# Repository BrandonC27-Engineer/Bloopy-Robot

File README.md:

# Bloopy 🤖
### An AI Companion Robot Prototype

**Designed and built by Brandon Carmona Guerena**

Bloopy is a personal robotics project exploring how electronics,
physical interaction, and artificial intelligence can work together
to create a more expressive companion.

The project began with an idea: What if a digital companion could
eventually have a physical presence and interact with its surroundings?

I developed a stationary working prototype to explore that idea,
combining custom hardware, sensors, a Raspberry Pi, an ESP32,
animated eyes, and an AI-assisted companion application.

---

## What the Prototype Does

The stationary Bloopy prototype integrates:

- **ESP32:** Collects sensor readings and controls OLED eye animations.
- **Raspberry Pi 4:** Handles higher-level processing and connected peripherals.
- **Sensors:** Detect environmental conditions and nearby objects.
- **OLED eyes:** Display expressions and animations in response to interactions.
- **Camera and microphone:** Support visual and audio input.
- **Speaker:** Provides audio output.
- **Companion application:** Provides controls, displays information, and
  communicates with the robot.
- **AI API integration:** Supports context-aware companion responses.

The application and hardware communicate to create an interactive
experience rather than a standalone chatbot.

## My Design and Building Process

I developed Bloopy through an iterative process involving:

1. Planning the robot's capabilities and component architecture.
2. Designing a stationary stand using Fusion 360.
3. Designing custom printed circuit boards using KiCad.
4. Assembling and connecting electronic components.
5. Integrating the ESP32 and Raspberry Pi.
6. Developing and refining software with AI assistance.
7. Testing the hardware and troubleshooting connections and behavior.

One of the greatest challenges was integrating hardware and software
into a system that behaved as intended.

## Custom PCB Designs

I designed two different PCBs:

### BloopyPrototype — Triangular PCB

Created for the stationary prototype.

This board was assembled and used successfully in the working prototype.

### BloopyHardware — Rectangular PCB

Designed for a proposed future mobile Bloopy design.

The board was manufactured but has not been assembled or validated
as a working electronic system.

**The two designs represent different stages of development,
not two completed robots.**

## 3D-Printed Stand

`BloopyPrototype.3mf`

The stand was designed in Fusion 360 to support the stationary
robot prototype and its components.

It represents the physical structure used during prototype development.

---

## Repository Structure

### `Bloopy-App-Reconstructed/`

Recovered and reconstructed application source files.

These files document application structure and development work.
They should not be interpreted as a byte-for-byte copy of every
file used in the original running application.

### `Arduino-Uno-R3/`

Reconstructed Arduino Uno R3 example code based on the project's
documented behavior.

The original project used an ultrasonic distance sensor,
a keypad, and an LCD display.

### `PCB-Additional-Schematics/`

Original KiCad design resources for both custom PCB projects.

Each PCB project includes:

- `.kicad_pcb` — PCB layout
- `.kicad_sch` — Circuit schematic
- `.kicad_pro` — KiCad project settings

### `BloopyPrototype.3mf`

Original 3D CAD model of the stationary Bloopy stand.

### `SOURCE_NOTES.md`

Additional information about source recovery, reconstruction,
and the status of the uploaded files.

---

## Arduino Projects: Where My Electronics Journey Began

Before Bloopy, I learned foundational electronics and programming
through an Arduino course.

After completing the course, I independently adapted earlier code
examples to combine:

- An Arduino Uno R3
- An ultrasonic distance sensor
- An LCD display
- A keypad

The program displayed sensor measurements in the serial monitor
and keypad input on the LCD.

I also attempted a larger Arduino Mega project with multiple sensors.

That second project was unsuccessful because of difficulties with
soldering and electrical connections. Although I did not finish it,
the experience motivated me to learn better assembly techniques.

These experiences helped me understand how individual electronic
components communicate and function together.

---

## Development Tools

- Fusion 360 — Mechanical CAD
- KiCad — PCB and schematic design
- Arduino IDE — Microcontroller development
- ESP32 — Embedded hardware control
- Raspberry Pi — Computing and peripheral integration
- Python and web development technologies
- AI-assisted software development tools

## AI Assistance and Source Transparency

I used AI tools, including Claude, to assist with portions of
software development.

My role included defining requirements, specifying behavior,
reviewing generated implementations, requesting changes,
integrating components, and troubleshooting the system.

Some software in this repository was reconstructed after the
original development process. Reconstructed files are identified
as such and should not be represented as the exact original
deployed source code.

The original ESP32 firmware used in the working prototype is
not included in this recovered source collection.

For details, see `SOURCE_NOTES.md`.

---

## Current Status and Future Goals

**Completed:** Functional stationary Bloopy prototype integrating
custom electronics, sensors, animated eyes, Raspberry Pi processing,
and a companion application.

**Future development:** Improving physical expressiveness,
exploring mobility, and developing more continuous character
animations that make Bloopy feel alive.

My long-term goal is to continue learning how mechanical design,
electronics, and software can come together in complete robotic systems.

---

## About the Builder

I'm Brandon Carmona Guerena, a high school student in Phoenix,
Arizona, interested in robotics and engineering.

I enjoy learning by building, experimenting, making mistakes,
and improving my designs.

[Visit my GitHub profile](https://github.com/BrandonC27-Engineer)

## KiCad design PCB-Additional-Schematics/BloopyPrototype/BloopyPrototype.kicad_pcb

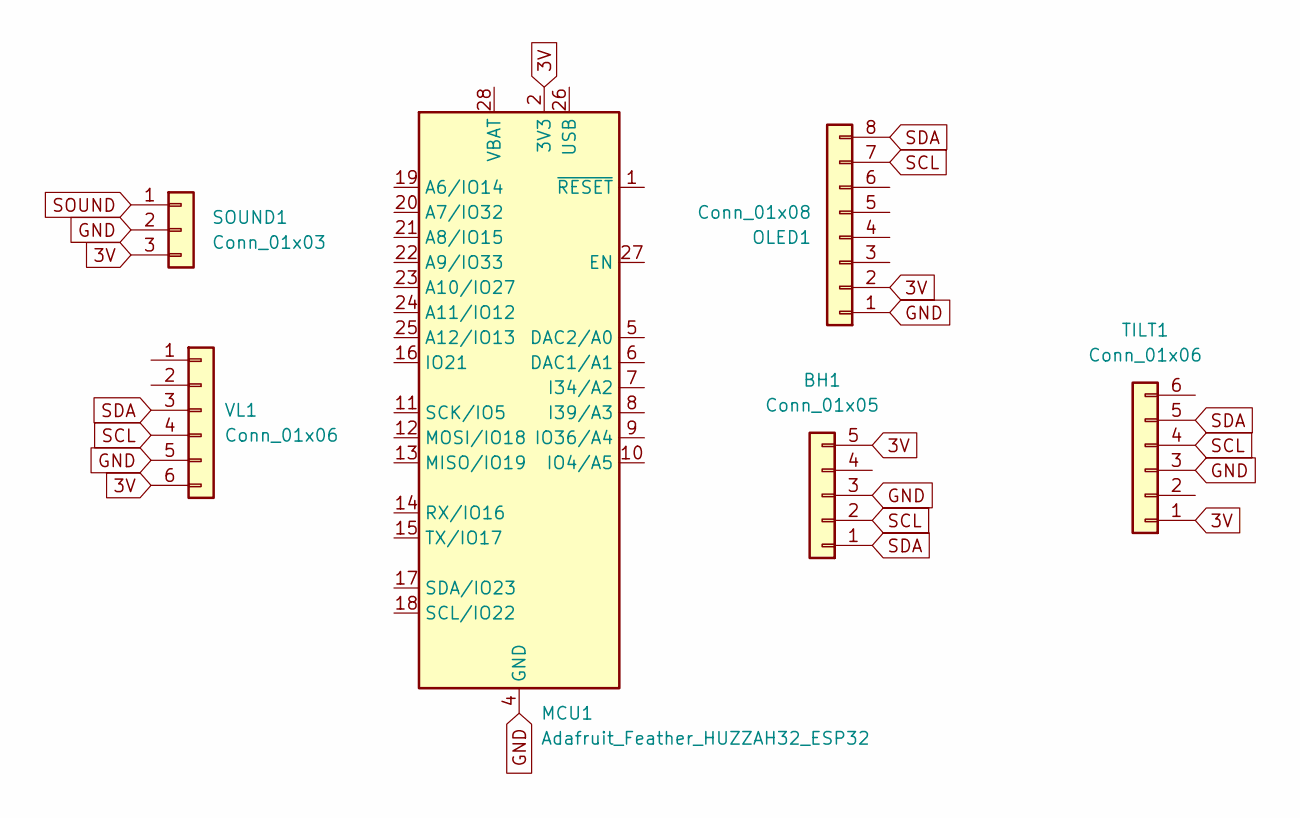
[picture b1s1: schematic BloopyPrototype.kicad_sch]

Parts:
BH1: Conn_01x05
MCU1: Adafruit_Feather_HUZZAH32_ESP32; Adafruit_Feather
OLED1: Conn_01x08
SOUND1: Conn_01x03
TILT1: Conn_01x06
VL1: Conn_01x06

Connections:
3V: BH1.5, MCU1.2 (3V3), OLED1.2, SOUND1.3, TILT1.1, VL1.6
GND: BH1.3, MCU1.4 (GND), OLED1.1, SOUND1.2, TILT1.3, VL1.5
SCL: BH1.2, MCU1.18 (SCL/IO22), OLED1.7, TILT1.4, VL1.4
SDA: BH1.1, MCU1.17 (SDA/IO23), OLED1.8, TILT1.5, VL1.3
SOUND: MCU1.7 (I34/A2), SOUND1.1

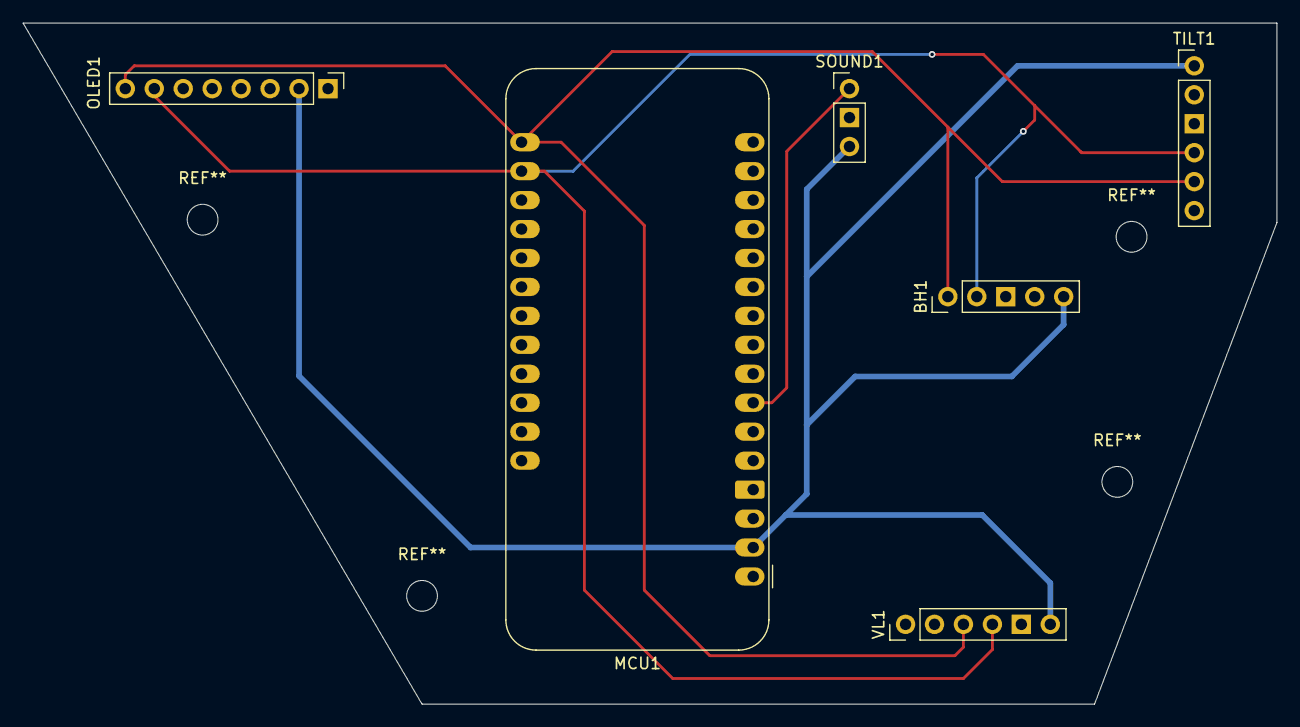
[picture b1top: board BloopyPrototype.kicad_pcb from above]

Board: 2 copper layers, 110.0 x 59.8 mm, 6 parts (0 on the bottom side), 5 nets.

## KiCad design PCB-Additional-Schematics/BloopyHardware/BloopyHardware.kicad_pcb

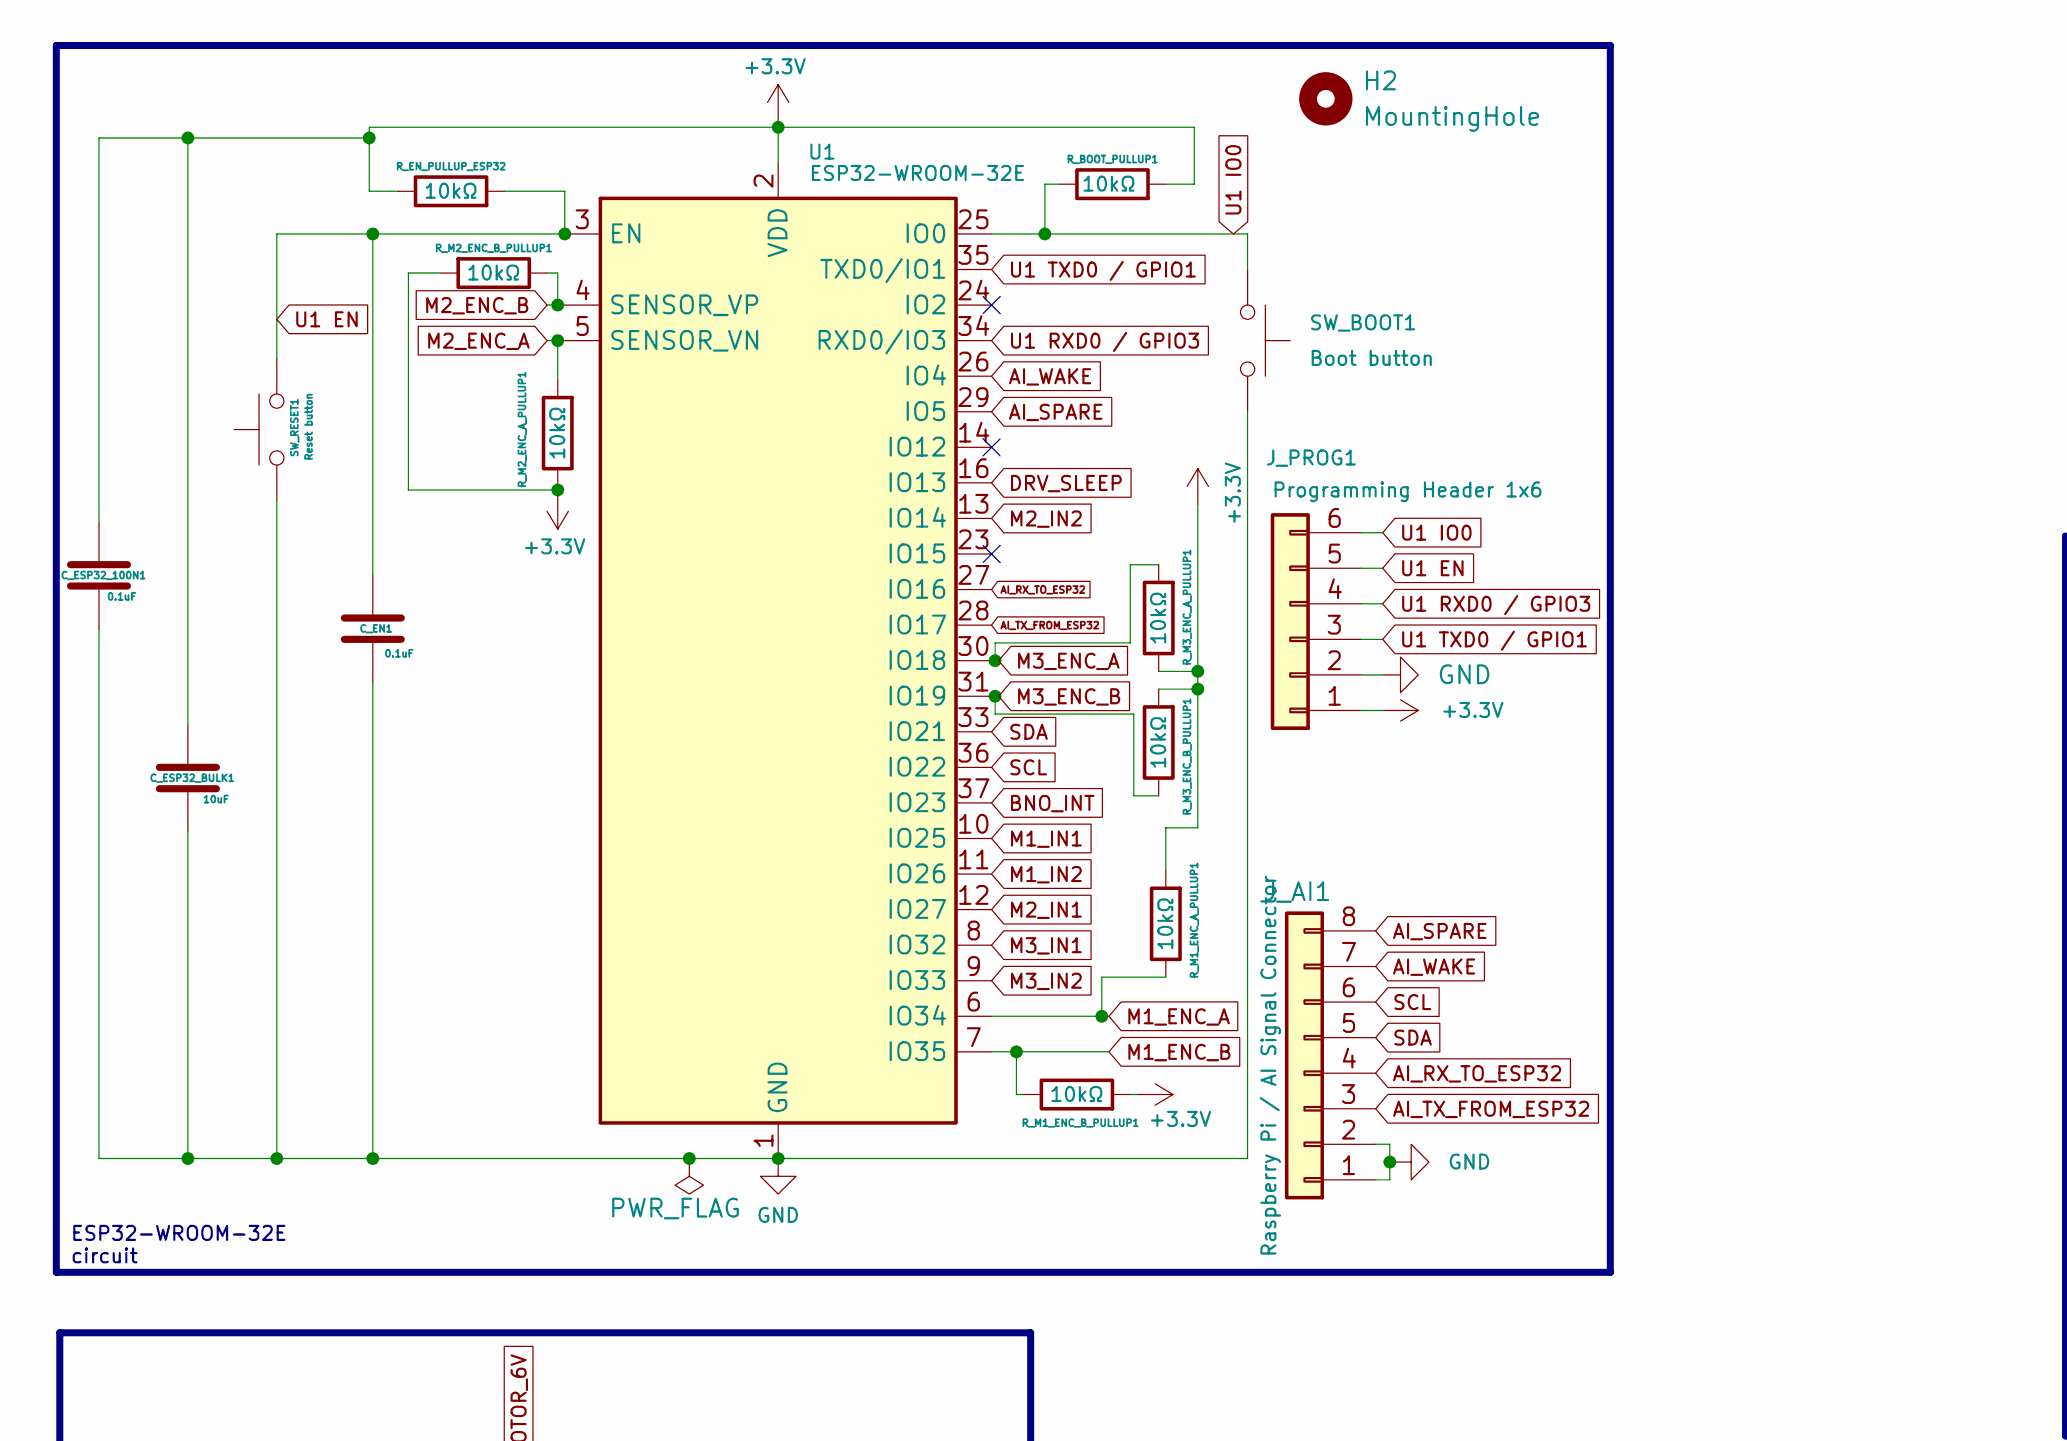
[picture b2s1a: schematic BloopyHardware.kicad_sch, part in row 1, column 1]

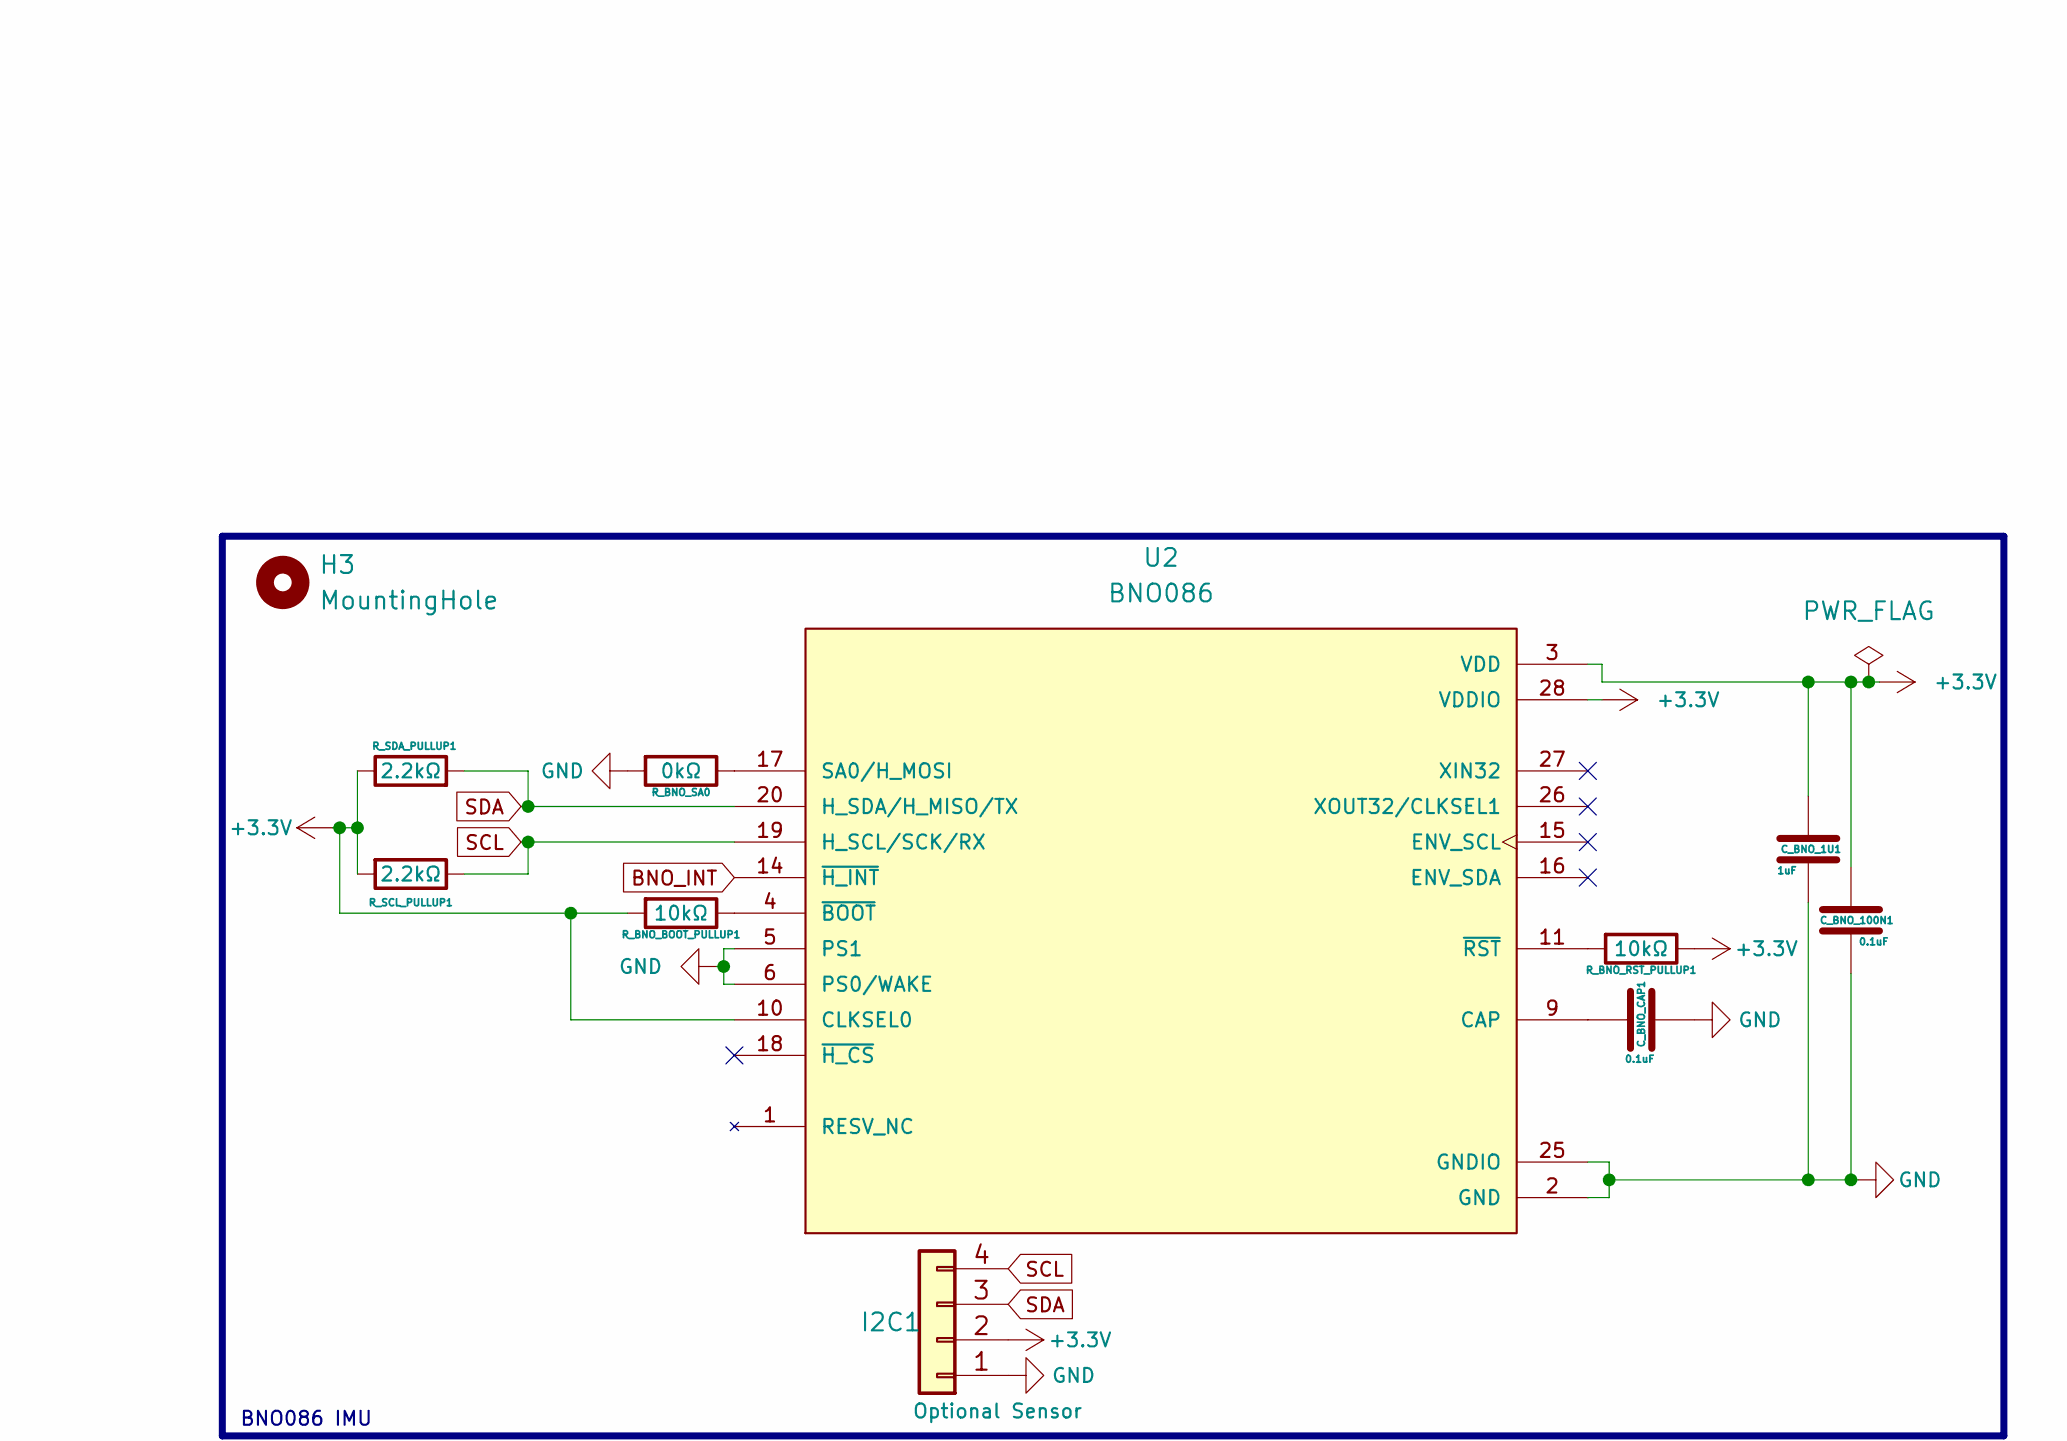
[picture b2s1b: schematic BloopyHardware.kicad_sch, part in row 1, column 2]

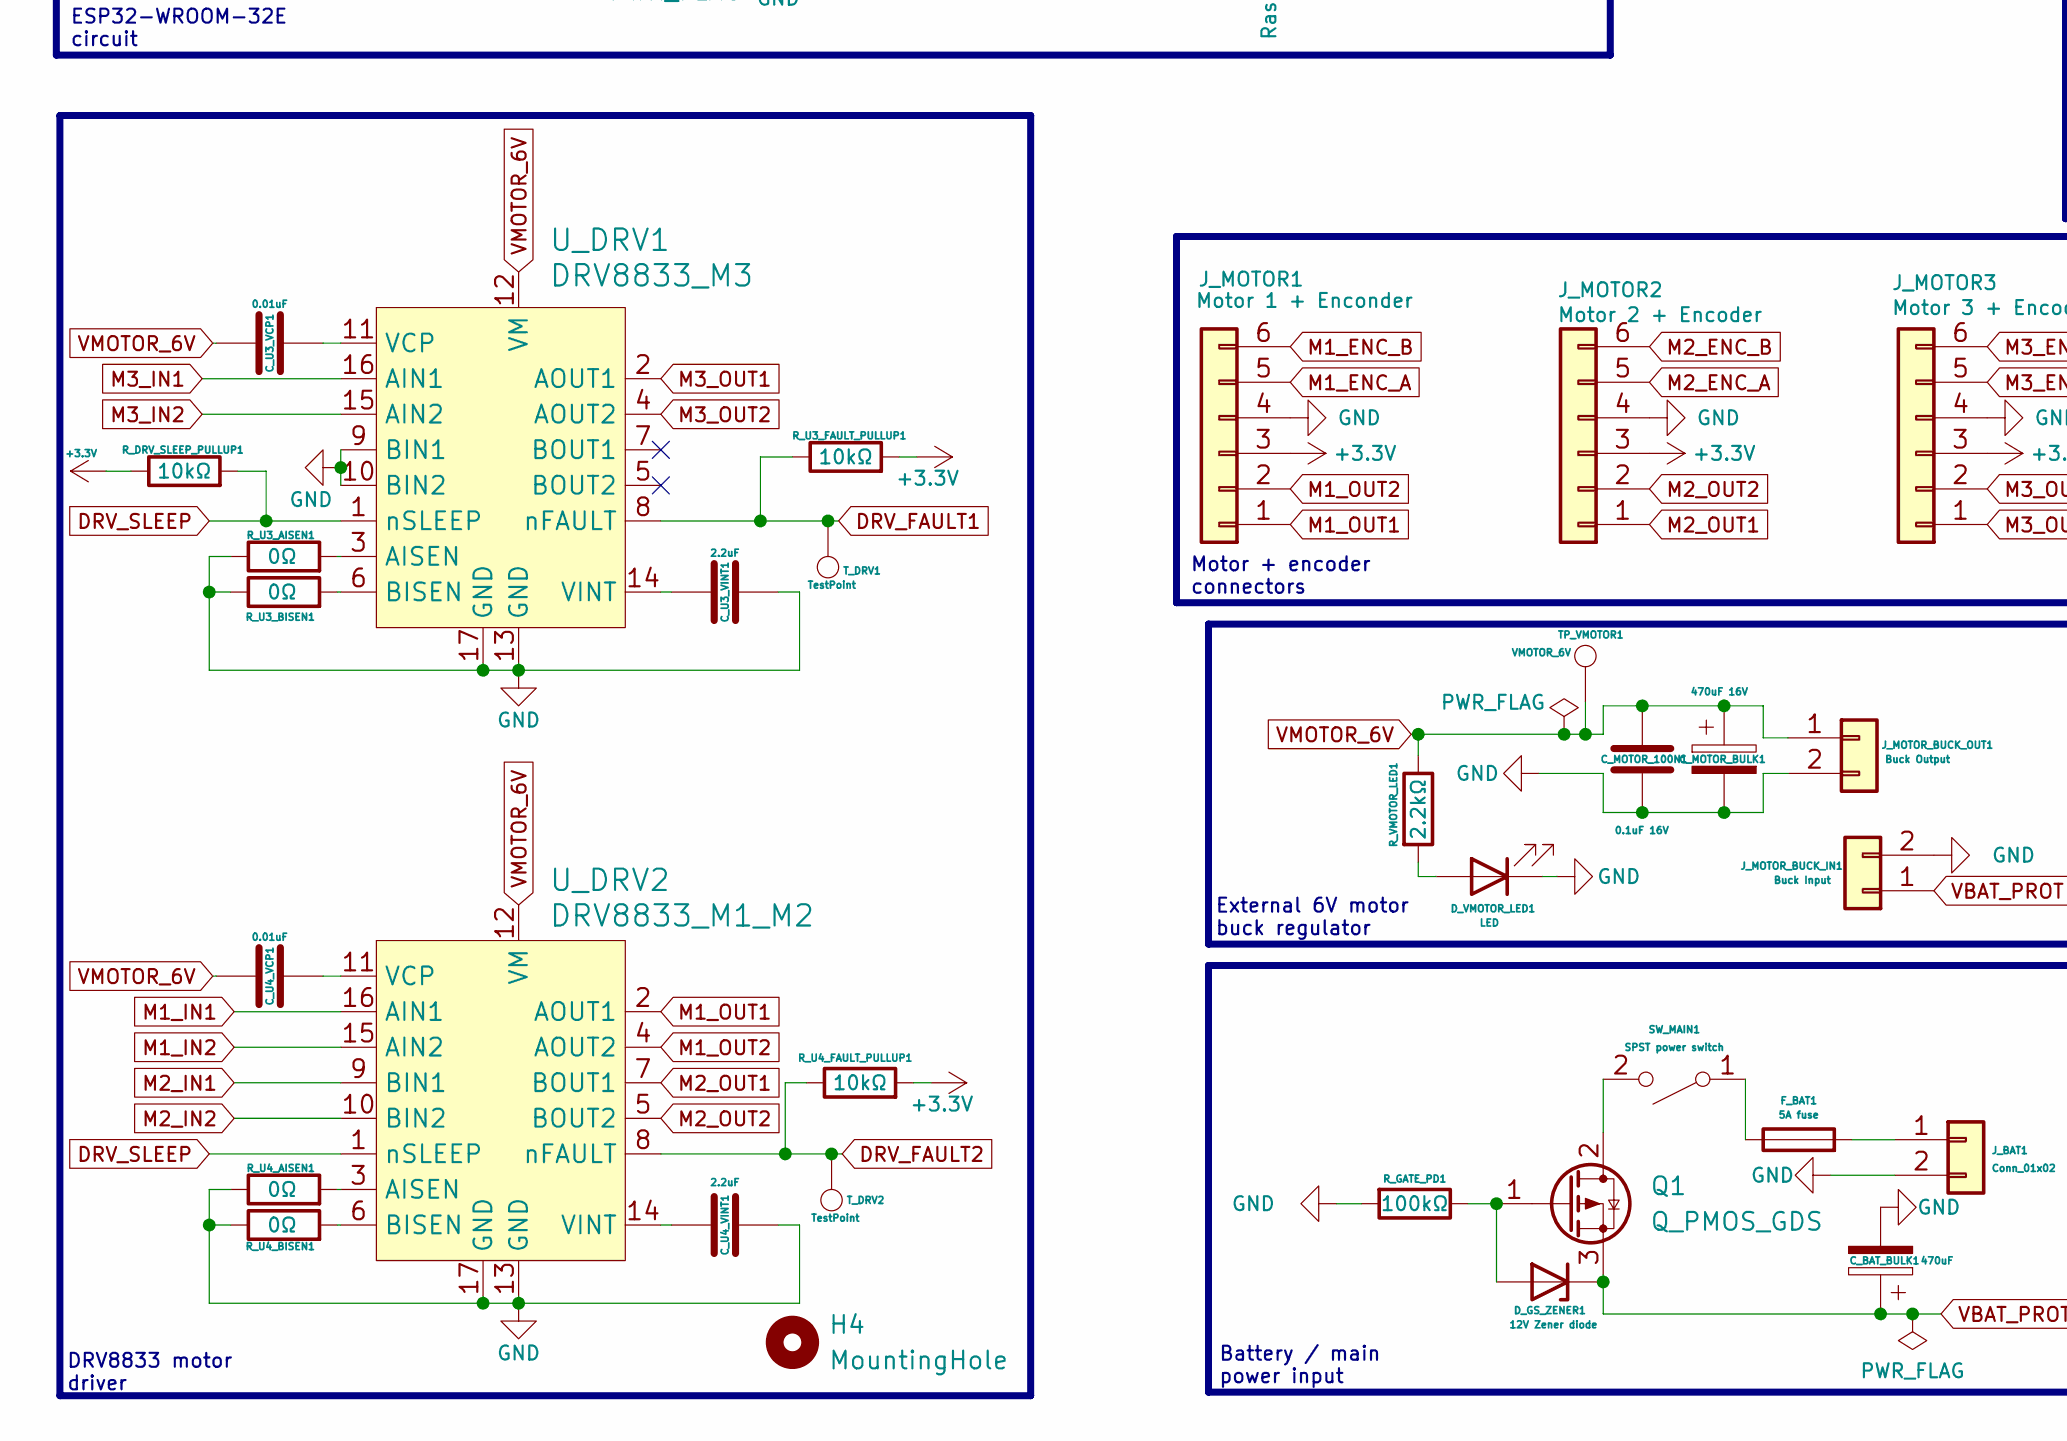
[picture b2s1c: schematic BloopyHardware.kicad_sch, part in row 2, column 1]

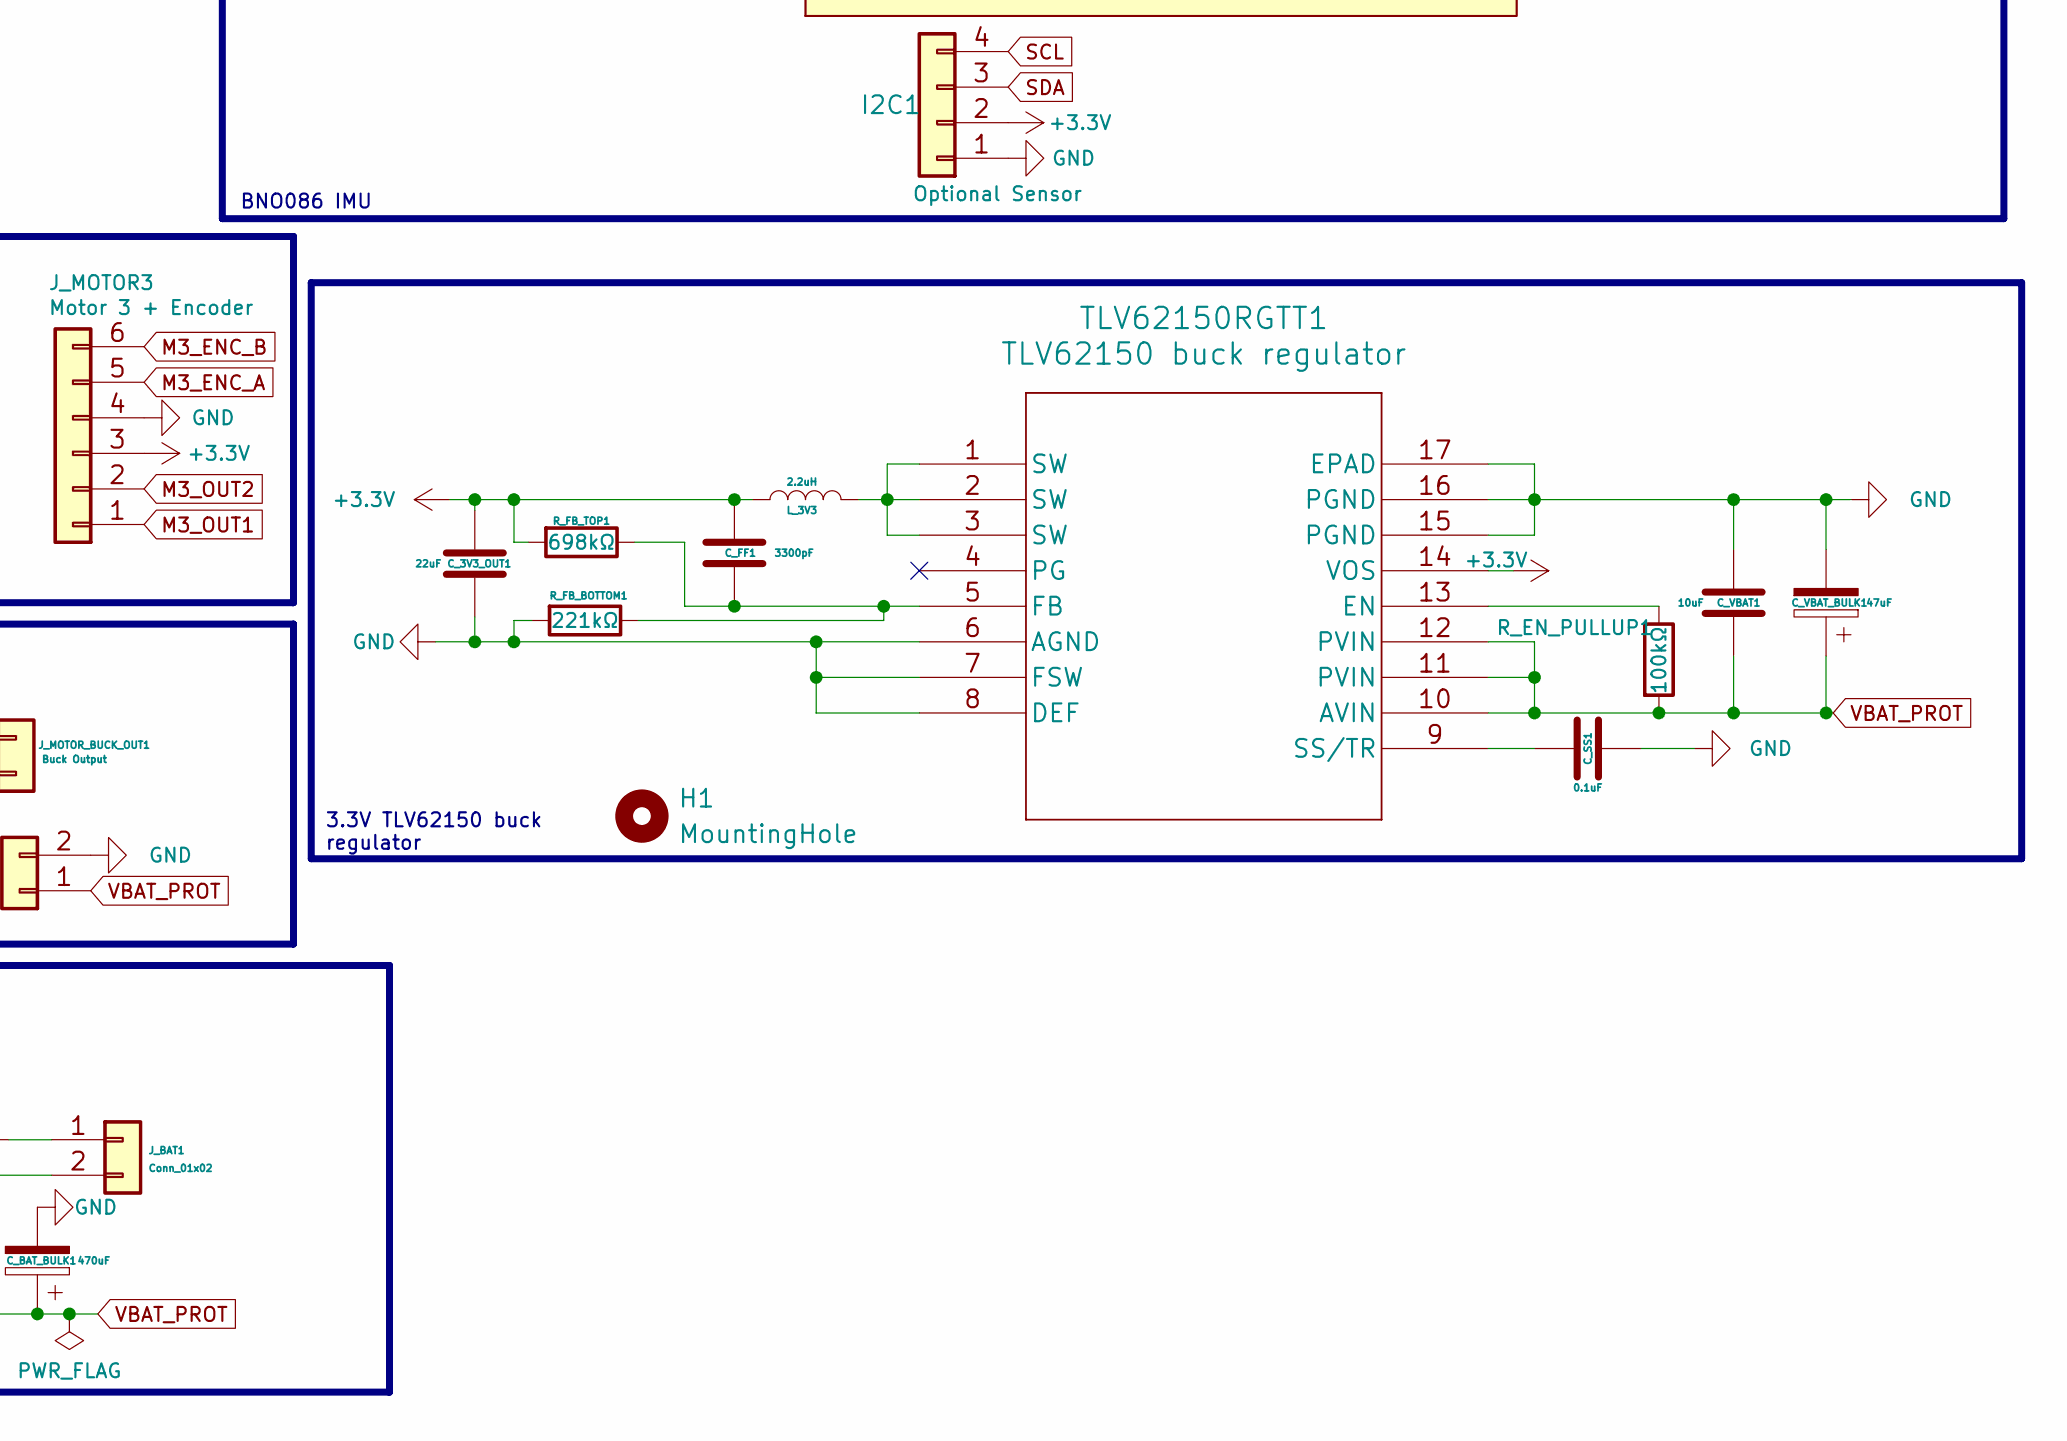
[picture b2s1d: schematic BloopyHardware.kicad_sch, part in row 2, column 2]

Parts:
C_3V3_OUT1: 22uF; C_0805_2012Metric
C_BAT_BULK1: 470uF; CP_Radial_D8.0mm_P3.50mm
C_BNO_1U1: 1uF; C_0805_2012Metric
C_BNO_100N1: 0.1uF; C_0805_2012Metric
C_BNO_CAP1: 0.1uF; C_0805_2012Metric
C_EN1: 0.1uF; C_0805_2012Metric
C_ESP32_100N1: 0.1uF; C_0805_2012Metric
C_ESP32_BULK1: 10uF; C_0805_2012Metric
C_FF1: 3300pF; C_0603_1608Metric
C_MOTOR_100N1: 0.1uF 16V; C_0805_2012Metric
C_MOTOR_BULK1: 470uF 16V; CP_Radial_D8.0mm_P3.50mm
C_SS1: 0.1uF; C_0603_1608Metric
C_U3_VCP1, C_U4_VCP1: 0.01uF; C_0805_2012Metric
C_U3_VINT1, C_U4_VINT1: 2.2uF; C_0805_2012Metric
C_VBAT1: 10uF; C_0805_2012Metric
C_VBAT_BULK1: 47uF; CP_Elec_6.3x5.8
D_GS_ZENER1: 12V Zener diode; D_SOD-123
D_VMOTOR_LED1: LED; LED_0805_2012Metric
F_BAT1: 5A fuse; Fuse_Blade_ATO_directSolder
H1, H2, H3, H4: MountingHole; MountingHole_3.2mm_M3
I2C1: Optional Sensor; PinHeader_1x04_P2.54mm_Vertical
J_AI1: Raspberry Pi / AI Signal Connector; PinHeader_1x08_P2.54mm_Vertical
J_BAT1: Conn_01x02; TerminalBlock_Phoenix_MKDS-1,5-2-5.08_1x02_P5.08mm_Horizont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
J_MOTOR1: Motor 1 + Enconder; JST_XH_B6B-XH-A_1x06_P2.50mm_Vertical
J_MOTOR2: Motor 2 + Encoder; JST_XH_B6B-XH-A_1x06_P2.50mm_Vertical
J_MOTOR3: Motor 3 + Encoder; JST_XH_B6B-XH-A_1x06_P2.50mm_Vertical
J_MOTOR_BUCK_IN1: Buck Input; TerminalBlock_Phoenix_MKDS-1,5-2-5.08_1x02_P5.08mm_Horizont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
J_MOTOR_BUCK_OUT1: Buck Output; TerminalBlock_Phoenix_MKDS-1,5-2-5.08_1x02_P5.08mm_Horizont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
J_PROG1: Programming Header 1x6; PinHeader_1x06_P2.54mm_Vertical
L_3V3: 2.2uH; IND_LQH44PN2R2MP0L
Q1: Q_PMOS_GDS; TO-252-3_TabPin2
R_BNO_BOOT_PULLUP1: 10kΩ; R_0805_2012Metric
R_BNO_RST_PULLUP1: 10kΩ; R_0805_2012Metric
R_BNO_SA0: 0kΩ; R_0805_2012Metric
R_BOOT_PULLUP1: 10kΩ; R_0805_2012Metric
R_DRV_SLEEP_PULLUP1: 10kΩ; R_0805_2012Metric
R_EN_PULLUP1: 100kΩ; R_0805_2012Metric
R_EN_PULLUP_ESP32: 10kΩ; R_0805_2012Metric
R_FB_BOTTOM1: 221kΩ; R_0805_2012Metric
R_FB_TOP1: 698kΩ; R_0805_2012Metric
R_GATE_PD1: 100kΩ; R_0805_2012Metric
R_M1_ENC_A_PULLUP1, R_M1_ENC_B_PULLUP1, R_M2_ENC_A_PULLUP1, R_M2_ENC_B_PULLUP1, R_M3_ENC_A_PULLUP1, R_M3_ENC_B_PULLUP1: 10kΩ; R_0805_2012Metric
R_SCL_PULLUP1: 2.2kΩ; R_0805_2012Metric
R_SDA_PULLUP1: 2.2kΩ; R_0805_2012Metric
R_U3_AISEN1, R_U3_BISEN1, R_U4_AISEN1, R_U4_BISEN1: 0Ω; R_0805_2012Metric
R_U3_FAULT_PULLUP1, R_U4_FAULT_PULLUP1: 10kΩ; R_0805_2012Metric
R_VMOTOR_LED1: 2.2kΩ; R_0805_2012Metric
SW_BOOT1: Boot button; SW_SPST_TL3342
SW_MAIN1: SPST power switch; PinHeader_1x02_P2.54mm_Vertical
SW_RESET1: Reset button; SW_SPST_TL3342
TLV62150RGTT1: TLV62150 buck regulator; VQFN-16-1EP_3x3mm_P0.5mm_EP1.6x1.6mm
TP_VMOTOR1: VMOTOR_6V; TestPoint_Pad_D1.5mm
T_DRV1, T_DRV2: TestPoint; TestPoint_Pad_D1.5mm
U1: ESP32-WROOM-32E
U2: BNO086; IC_BNO086; PARTREV v1.17
U_DRV1: DRV8833_M3; TSSOP-16-1EP_W4.40mm; MPN DRV8833PWPR; Digi-Key_PN 296-29434-1-ND
U_DRV2: DRV8833_M1_M2; TSSOP-16-1EP_W4.40mm; MPN DRV8833PWPR; Digi-Key_PN 296-29434-1-ND

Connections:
+3.3V: C_3V3_OUT1.1, C_BNO_1U1.1, C_BNO_100N1.1, C_ESP32_100N1.1, C_ESP32_BULK1.1, C_FF1.1, I2C1.2, J_MOTOR1.3, J_MOTOR2.3, J_MOTOR3.3, J_PROG1.1, L_3V3.1, R_BNO_BOOT_PULLUP1.2, R_BNO_RST_PULLUP1.1, R_BOOT_PULLUP1.2, R_DRV_SLEEP_PULLUP1.1, R_EN_PULLUP_ESP32.1, R_FB_TOP1.2, R_M1_ENC_A_PULLUP1.2, R_M1_ENC_B_PULLUP1.2, R_M2_ENC_A_PULLUP1.1, R_M2_ENC_B_PULLUP1.2, R_M3_ENC_A_PULLUP1.1, R_M3_ENC_B_PULLUP1.2, R_SCL_PULLUP1.2, R_SDA_PULLUP1.1, R_U3_FAULT_PULLUP1.2, R_U4_FAULT_PULLUP1.2, TLV62150RGTT1.14 (VOS), U1.2 (VDD), U2.3 (VDD), U2.10 (CLKSEL0), U2.28 (VDDIO)
AI_RX_TO_ESP32: J_AI1.4, U1.27 (IO16)
AI_SPARE: J_AI1.8, U1.29 (IO5)
AI_TX_FROM_ESP32: J_AI1.3, U1.28 (IO17)
AI_WAKE: J_AI1.7, U1.26 (IO4)
BNO_INT: U1.37 (IO23), U2.14 (~H_INT)
DRV_FAULT1: R_U3_FAULT_PULLUP1.1, T_DRV1.1, U_DRV1.8 (nFAULT)
DRV_FAULT2: R_U4_FAULT_PULLUP1.1, T_DRV2.1, U_DRV2.8 (nFAULT)
DRV_SLEEP: R_DRV_SLEEP_PULLUP1.2, U1.16 (IO13), U_DRV1.1 (nSLEEP), U_DRV2.1 (nSLEEP)
GND: C_3V3_OUT1.2, C_BAT_BULK1.2, C_BNO_1U1.2, C_BNO_100N1.2, C_BNO_CAP1.2, C_EN1.2, C_ESP32_100N1.2, C_ESP32_BULK1.2, C_MOTOR_100N1.2, C_MOTOR_BULK1.2, C_SS1.2, C_U3_VINT1.2, C_U4_VINT1.2, C_VBAT1.1, C_VBAT_BULK1.2, D_VMOTOR_LED1.1 (K), I2C1.1, J_AI1.1, J_AI1.2, J_BAT1.2, J_MOTOR1.4, J_MOTOR2.4, J_MOTOR3.4, J_MOTOR_BUCK_IN1.2, J_MOTOR_BUCK_OUT1.2, J_PROG1.2, R_BNO_SA0.2, R_FB_BOTTOM1.2, R_GATE_PD1.2, R_U3_AISEN1.1, R_U3_BISEN1.1, R_U4_AISEN1.1, R_U4_BISEN1.1, SW_BOOT1.2, SW_RESET1.1, TLV62150RGTT1.6 (AGND), TLV62150RGTT1.7 (FSW), TLV62150RGTT1.8 (DEF), TLV62150RGTT1.15 (PGND), TLV62150RGTT1.16 (PGND), TLV62150RGTT1.17 (EPAD), U1.1 (GND), U1.15 (GND), U1.38 (GND), U1.39 (GND), U2.2 (GND), U2.5 (PS1), U2.6 (PS0/WAKE), U2.25 (GNDIO), U_DRV1.9 (BIN1), U_DRV1.10 (BIN2), U_DRV1.13 (GND), U_DRV1.17 (GND), U_DRV2.13 (GND), U_DRV2.17 (GND)
M1_ENC_A: J_MOTOR1.5, R_M1_ENC_A_PULLUP1.1, U1.6 (IO34)
M1_ENC_B: J_MOTOR1.6, R_M1_ENC_B_PULLUP1.1, U1.7 (IO35)
M1_IN1: U1.10 (IO25), U_DRV2.16 (AIN1)
M1_IN2: U1.11 (IO26), U_DRV2.15 (AIN2)
M1_OUT1: J_MOTOR1.1, U_DRV2.2 (AOUT1)
M1_OUT2: J_MOTOR1.2, U_DRV2.4 (AOUT2)
M2_ENC_A: J_MOTOR2.5, R_M2_ENC_A_PULLUP1.2, U1.5 (SENSOR_VN)
M2_ENC_B: J_MOTOR2.6, R_M2_ENC_B_PULLUP1.1, U1.4 (SENSOR_VP)
M2_IN1: U1.12 (IO27), U_DRV2.9 (BIN1)
M2_IN2: U1.13 (IO14), U_DRV2.10 (BIN2)
M2_OUT1: J_MOTOR2.1, U_DRV2.7 (BOUT1)
M2_OUT2: J_MOTOR2.2, U_DRV2.5 (BOUT2)
M3_ENC_A: J_MOTOR3.5, R_M3_ENC_A_PULLUP1.2, U1.30 (IO18)
M3_ENC_B: J_MOTOR3.6, R_M3_ENC_B_PULLUP1.1, U1.31 (IO19)
M3_IN1: U1.8 (IO32), U_DRV1.16 (AIN1)
M3_IN2: U1.9 (IO33), U_DRV1.15 (AIN2)
M3_OUT1: J_MOTOR3.1, U_DRV1.2 (AOUT1)
M3_OUT2: J_MOTOR3.2, U_DRV1.4 (AOUT2)
unnamed: D_GS_ZENER1.2 (A), Q1.1 (G), R_GATE_PD1.1
unnamed: D_VMOTOR_LED1.2 (A), R_VMOTOR_LED1.2
unnamed: F_BAT1.2, J_BAT1.1
unnamed: L_3V3.2, TLV62150RGTT1.1 (SW), TLV62150RGTT1.2 (SW), TLV62150RGTT1.3 (SW)
unnamed: Q1.2 (D), SW_MAIN1.2 (B)
unnamed: F_BAT1.1, SW_MAIN1.1 (A)
unnamed: R_EN_PULLUP1.1, TLV62150RGTT1.13 (EN)
unnamed: C_FF1.2, R_FB_BOTTOM1.1, R_FB_TOP1.1, TLV62150RGTT1.5 (FB)
unnamed: C_SS1.1, TLV62150RGTT1.9 (SS/TR)
unnamed: C_BNO_CAP1.1, U2.9 (CAP)
unnamed: R_BNO_SA0.1, U2.17 (SA0/H_MOSI)
unnamed: R_BNO_BOOT_PULLUP1.1, U2.4 (~BOOT)
unnamed: R_BNO_RST_PULLUP1.2, U2.11 (~RST)
unnamed: R_U3_AISEN1.2, U_DRV1.3 (AISEN)
unnamed: R_U3_BISEN1.2, U_DRV1.6 (BISEN)
unnamed: C_U3_VCP1.2, U_DRV1.11 (VCP)
unnamed: C_U3_VINT1.1, U_DRV1.14 (VINT)
unnamed: R_U4_AISEN1.2, U_DRV2.3 (AISEN)
unnamed: R_U4_BISEN1.2, U_DRV2.6 (BISEN)
unnamed: C_U4_VCP1.2, U_DRV2.11 (VCP)
unnamed: C_U4_VINT1.1, U_DRV2.14 (VINT)
SCL: I2C1.4, J_AI1.6, R_SCL_PULLUP1.1, U1.36 (IO22), U2.19 (H_SCL/SCK/RX)
SDA: I2C1.3, J_AI1.5, R_SDA_PULLUP1.2, U1.33 (IO21), U2.20 (H_SDA/H_MISO/TX)
U1 EN: C_EN1.1, J_PROG1.5, R_EN_PULLUP_ESP32.2, SW_RESET1.2, U1.3 (EN)
U1 IO0: J_PROG1.6, R_BOOT_PULLUP1.1, SW_BOOT1.1, U1.25 (IO0)
U1 RXD0 / GPIO3: J_PROG1.4, U1.34 (RXD0/IO3)
U1 TXD0 / GPIO1: J_PROG1.3, U1.35 (TXD0/IO1)
VBAT_PROT: C_BAT_BULK1.1, C_VBAT1.2, C_VBAT_BULK1.1, D_GS_ZENER1.1 (K), J_MOTOR_BUCK_IN1.1, Q1.3 (S), R_EN_PULLUP1.2, TLV62150RGTT1.10 (AVIN), TLV62150RGTT1.11 (PVIN), TLV62150RGTT1.12 (PVIN)
VMOTOR_6V: C_MOTOR_100N1.1, C_MOTOR_BULK1.1, C_U3_VCP1.1, C_U4_VCP1.1, J_MOTOR_BUCK_OUT1.1, R_VMOTOR_LED1.1, TP_VMOTOR1.1, U_DRV1.12 (VM), U_DRV2.12 (VM)

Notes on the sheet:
3.3V TLV62150 buck regulator
Battery / main power input
External 6V motor buck regulator
BNO086 IMU
DRV8833 motor driver
Motor + encoder connectors
ESP32-WROOM-32E circuit
